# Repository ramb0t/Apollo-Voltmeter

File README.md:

Apollo-Voltmeter
================

Voltmeter Code for Design Two Module

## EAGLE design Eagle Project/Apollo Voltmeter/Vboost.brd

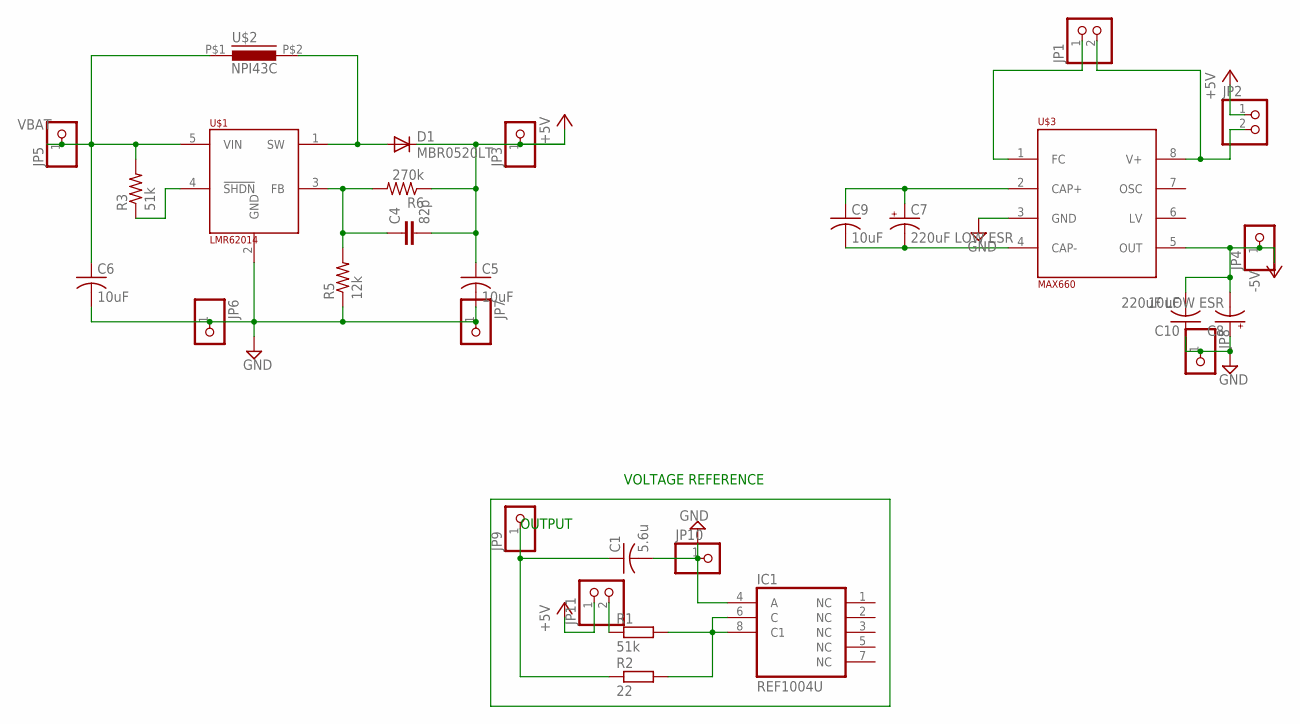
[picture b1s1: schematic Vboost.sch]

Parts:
C1: 5.6u; C0805K
C4: 82p; C0805
C5, C6, C9, C10: 10uF; C0805
C7, C8: 220uF LOW ESR; PANASONIC_D
D1: MBR0520LT; SOD123
IC1: REF1004U; SO08
JP1, JP2, JP11: PINHD-1X2; 1X02
JP3, JP4, JP5, JP6, JP7, JP8, JP9, JP10: PINHD-1X1; 1X01
R1: 51k; M0805
R2: 22; M0805
R3: 51k; R0805
R5: 12k; R0805
R6: 270k; R0805
U$1: LMR62014; SOT23-5
U$2: NPI43C
U$3: MAX660; SO08

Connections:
+5V: C4.2, C5.1, D1.C, JP2.1, JP3.1, JP11.1, R6.1
-5V: C8.-, C10.2, JP4.1, U$3.5 (OUT)
GND: C1.2, C5.2, C6.2, C8.+, C10.1, IC1.4 (A), JP6.1, JP7.1, JP8.1, JP10.1, R5.1, U$1.2 (GND), U$3.3 (GND)
unnamed: JP1.2, JP2.2, U$3.8 (V+)
unnamed: IC1.6 (C), IC1.8 (C1), R1.2, R2.2
unnamed: C1.1, JP9.1, R2.1
unnamed: C7.+, C9.1, U$3.2 (CAP+)
unnamed: JP11.2, R1.1
unnamed: R3.1, U$1.4 (!SHDN)
unnamed: C7.-, C9.2, U$3.4 (CAP-)
unnamed: C4.1, R5.2, R6.2, U$1.3 (FB)
unnamed: JP1.1, U$3.1 (FC)
SW: D1.A, U$1.1 (SW), U$2.P$2 (2)
VBAT: C6.1, JP5.1, R3.2, U$1.5 (VIN), U$2.P$1 (1)

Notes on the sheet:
OUTPUT
VOLTAGE REFERENCE

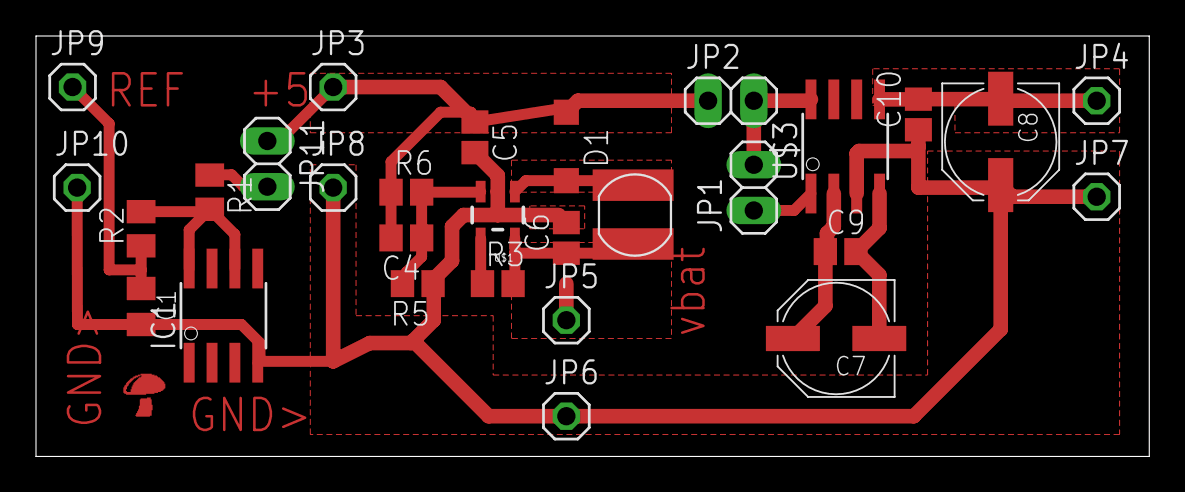
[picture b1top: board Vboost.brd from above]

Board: 2 copper layers, 61.8 x 23.4 mm, 29 parts (0 on the bottom side), 14 nets.

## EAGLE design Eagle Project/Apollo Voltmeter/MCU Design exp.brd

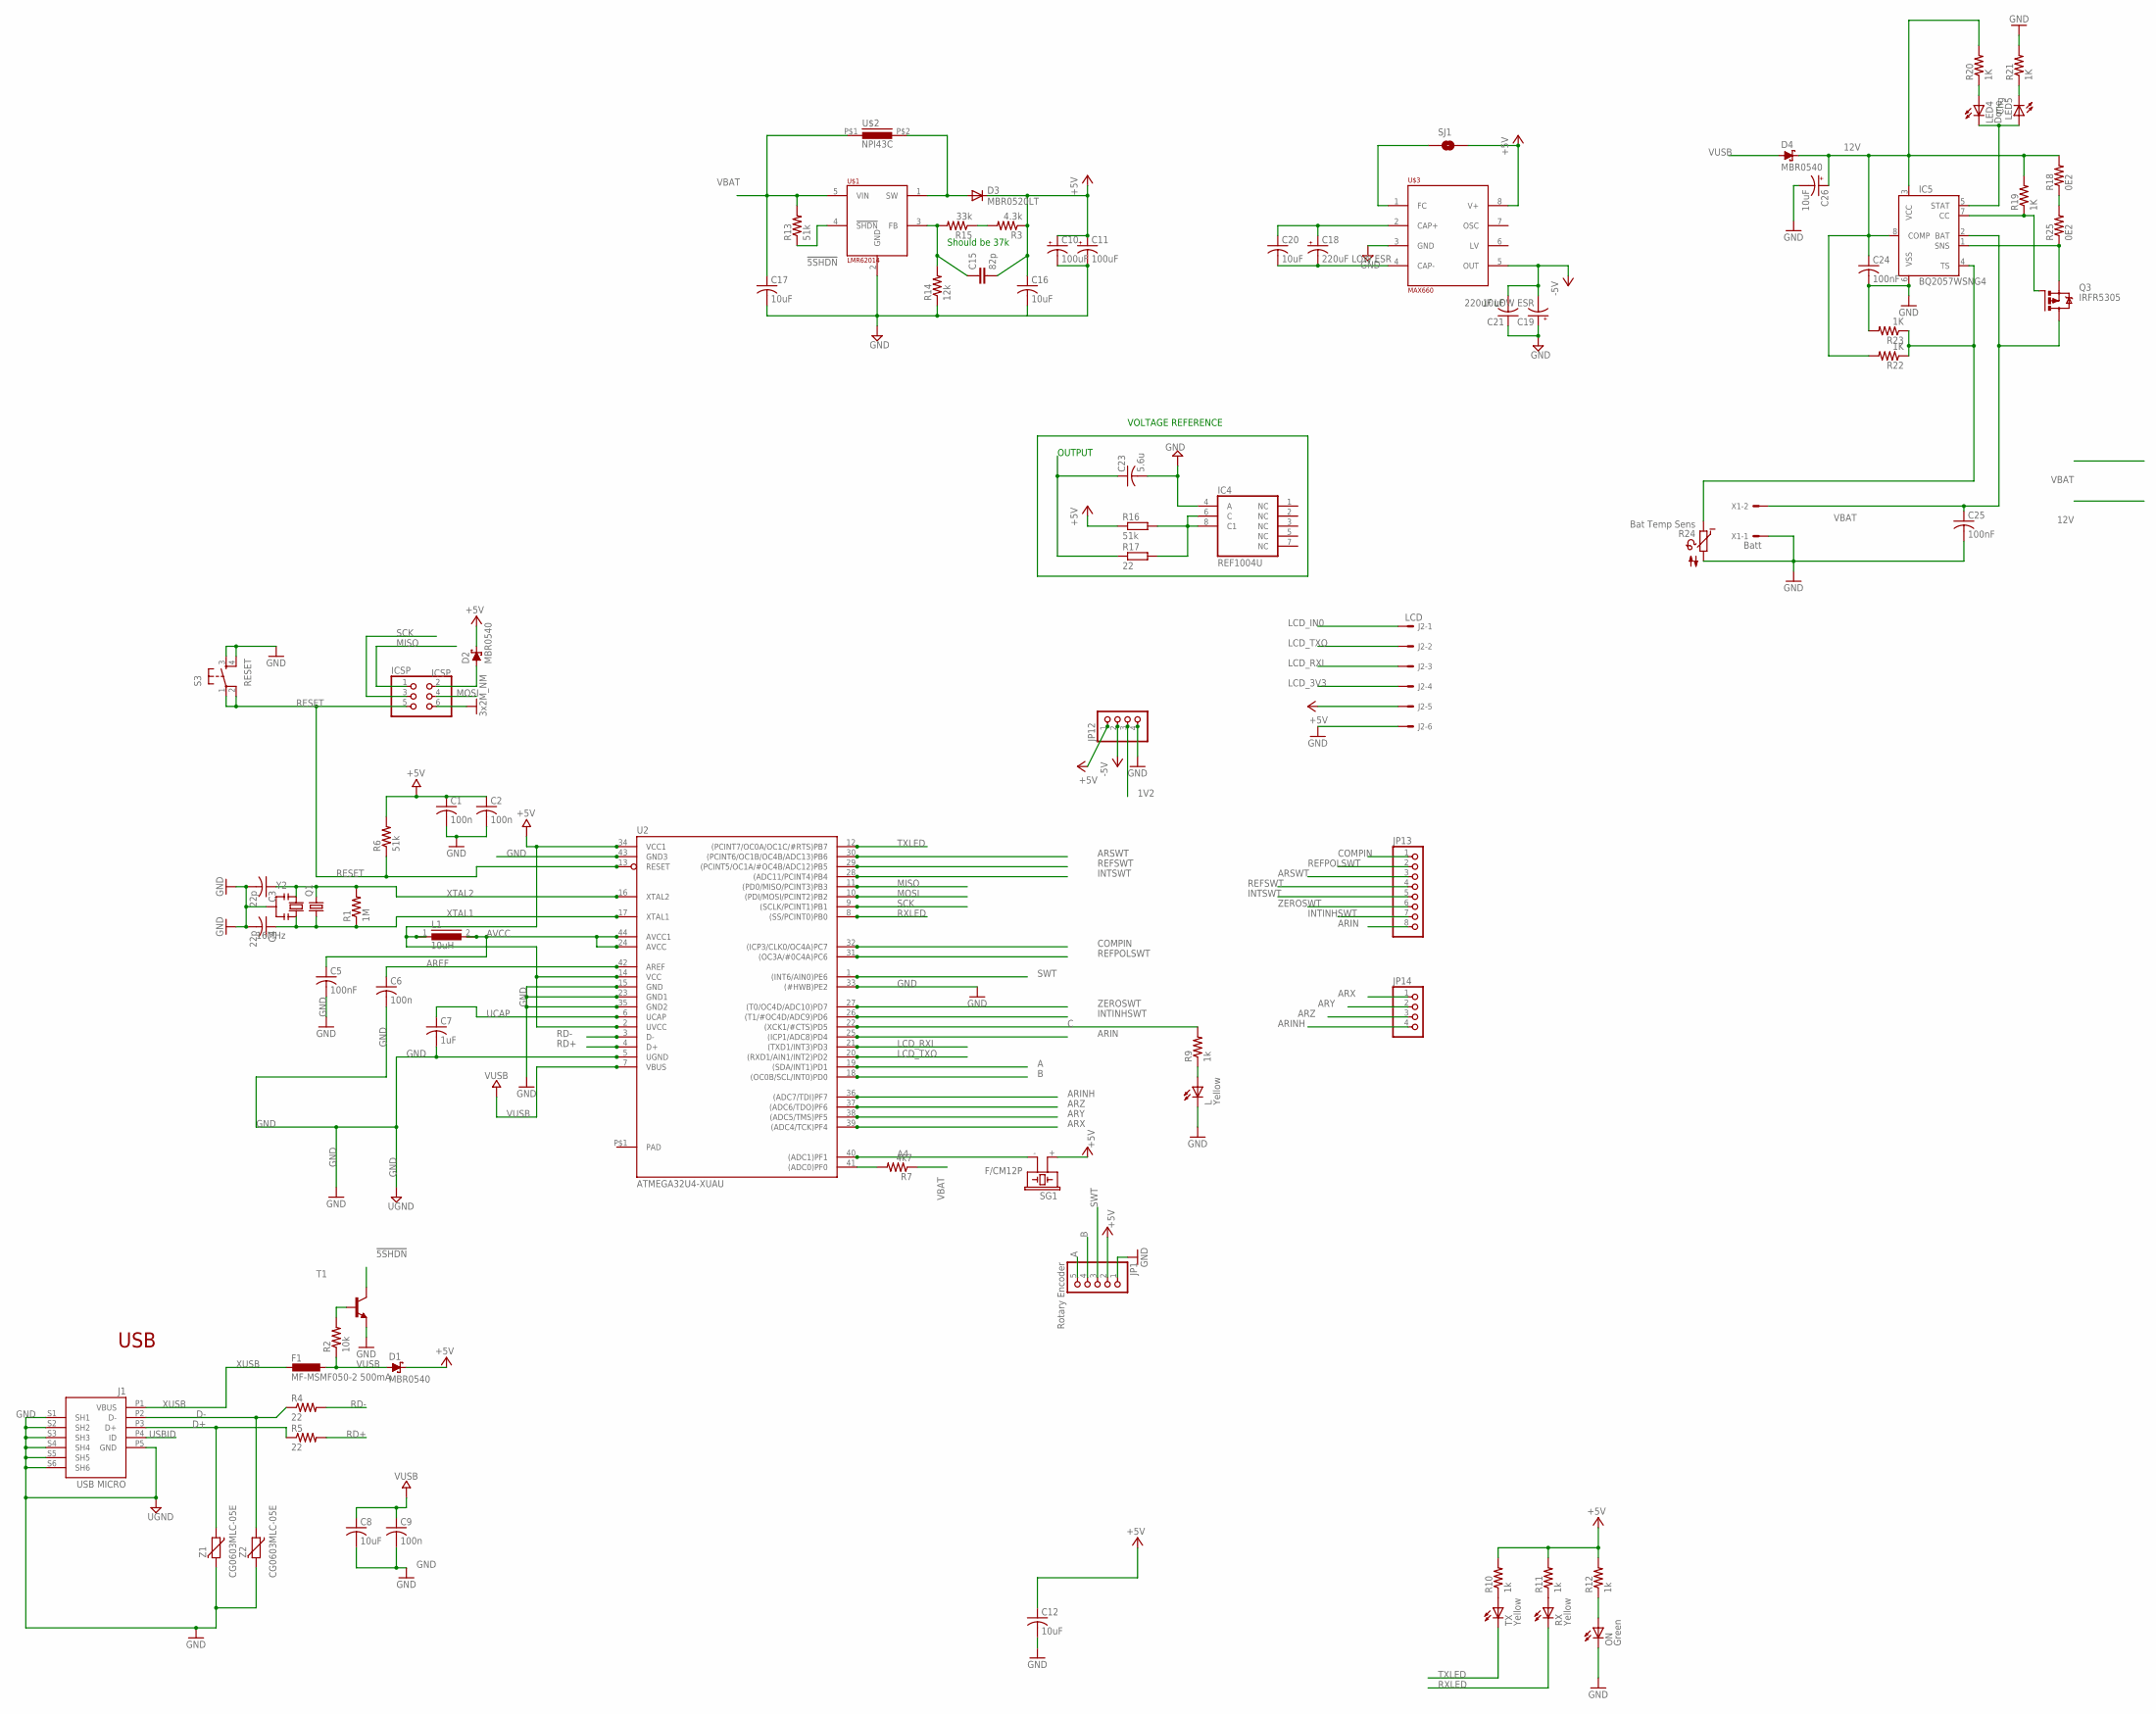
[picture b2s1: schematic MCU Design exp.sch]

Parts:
C1, C2, C6, C9: 100n; C0805
C3, C4: 22p; C0805
C5: 100nF; C0805
C7: 1uF; C0805
C8, C12, C16, C17, C20, C21: 10uF; C0805
C10, C11: 100uF; PANASONIC_D
C15: 82p; C0805
C18, C19: 220uF LOW ESR; PANASONIC_D
C23: 5.6u; C0805K
C24, C25: 100nF; C0805K
C26: 10uF; 153CLV-0405
D1, D2, D4: MBR0540; SOD123@2
D3: MBR0520LT; SOD123
F1: MF-MSMF050-2 500mA; L1812
IC4: REF1004U; SO08
IC5: BQ2057WSNG4; D_R-PDSO-G8
ICSP: ICSP; 2X03
J1: USB MICRO; CON2_USB_MICRO_B_AT
J2: LCD; 7395-06
JP1: Rotary Encoder; 1X05
JP12, JP14: PINHD-1X4; 1X04
JP13: PINHD-1X8; 1X08
L: Yellow; CHIPLED_0805
L1: 10uH; MMICC7
LED4: Done; CHIPLED_0805
LED5: Chg; CHIPLED_0805
ON: Green; CHIPLED_0805
Q1: CRYSTALHC49UP; HC49UP
Q3: IRFR5305; D-PAK_TO252AA
R1: 1M; R0805
R2: 10k; R0805
R3: 4.3k; R0805
R4, R5: 22; R0805
R6, R13: 51k; R0805
R7: 4k7; R0805
R9, R10, R11, R12: 1k; R0805
R14: 12k; R0805
R15: 33k; R0805
R16: 51k; M0805
R17: 22; M0805
R18, R25: 0E2; M1206
R19, R20, R21, R22, R23: 1K; R0805
R24: Bat Temp Sens; P640
RX: Yellow; CHIPLED_0805
S3: RESET; TACTILE_SWITCH_SMD
SG1: F/CM12P
SJ1: SOLDERJUMPERTRACE; SJ_2S-TRACE
T1: MMBT2222ALT1-NPN-SOT23-BEC; SOT23-BEC
TX: Yellow; CHIPLED_0805
U2: ATMEGA32U4-XUAU; TQFP44-PAD
U$1: LMR62014; SOT23-5
U$2: NPI43C
U$3: MAX660; SO08
X1: Batt; 22-23-2021
Y2: 16MHz; RESONATOR
Z1, Z2: CG0603MLC-05E; CT/CN0603

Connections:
1V2: C23.1, JP12.3, R17.1
12V: C24.1, C26.+, D4.C, IC5.3 (VCC), IC5.8 (COMP), R18.2, R19.2, R20.2, R22.2
!5SHDN: R13.1, T1.C, U$1.4 (!SHDN)
+5V: C1.1, C2.1, C10.+, C11.+, C12.1, C15.2, C16.1, D1.C, D2.C, D3.C, J2.5, JP1.2, JP12.1, L1.1, R3.1, R6.2, R10.2, R11.2, R12.2, R16.1, SG1.+ (1), SJ1.2, U2.2 (UVCC), U2.14 (VCC), U2.34 (VCC1), U$3.8 (V+)
-5V: C19.-, C21.2, JP12.2, U$3.5 (OUT)
A: JP1.5, U2.19 ((SDA/INT1)PD1)
A4: SG1.- (2), U2.40 ((ADC1)PF1)
AREF: C6.1, U2.42 (AREF)
ARIN: JP13.8, U2.25 ((ICP1/ADC8)PD4)
ARINH: JP14.4, U2.36 ((ADC7/TDI)PF7)
ARSWT: JP13.3, U2.30 ((PCINT6/OC1B/OC4B/ADC13)PB6)
ARX: JP14.1, U2.39 ((ADC4/TCK)PF4)
ARY: JP14.2, U2.38 ((ADC5/TMS)PF5)
ARZ: JP14.3, U2.37 ((ADC6/TDO)PF6)
AVCC: C5.1, L1.2, U2.24 (AVCC), U2.44 (AVCC1)
B: JP1.4, U2.18 ((OC0B/SCL/INT0)PD0)
C: R9.2, U2.22 ((XCK1/#CTS)PD5)
COMPIN: JP13.1, U2.32 ((ICP3/CLK0/OC4A)PC7)
D+: J1.P3 (D+), R5.1, Z1.1
D-: J1.P2 (D-), R4.1, Z2.1
GND: C1.2, C2.2, C3.2, C4.2, C5.2, C6.2, C7.2, C8.2, C9.2, C10.-, C11.-, C12.2, C16.2, C17.2, C19.+, C21.1, C23.2, C24.2, C25.2, C26.-, IC4.4 (A), IC5.6 (VSS), ICSP.6, J1.P5 (GND), J1.S1 (SH1), J1.S2 (SH2), J1.S3 (SH3), J1.S4 (SH4), J1.S5 (SH5), J1.S6 (SH6), J2.6, JP1.1, JP12.4, L.C, ON.C, R14.1, R21.2, R23.2, R24.2, S3.3, S3.4, T1.E, U2.5 (UGND), U2.15 (GND), U2.23 (GND1), U2.33 ((#HWB)PE2), U2.35 (GND2), U2.43 (GND3), U$1.2 (GND), U$3.3 (GND), X1.1, Y2.2, Z1.2, Z2.2
INTINHSWT: JP13.7, U2.26 ((T1/#OC4D/ADC9)PD6)
INTSWT: JP13.5, U2.28 ((ADC11/PCINT4)PB4)
LCD_3V3: J2.4
LCD_IN0: J2.1
LCD_RXI: J2.3, U2.21 ((TXD1/INT3)PD3)
LCD_TXO: J2.2, U2.20 ((RXD1/AIN1/INT2)PD2)
MISO: ICSP.1, U2.11 ((PD0/MISO/PCINT3)PB3)
MOSI: ICSP.4, U2.10 ((PDI/MOSI/PCINT2)PB2)
unnamed: R10.1, TX.A
unnamed: L.A, R9.1
unnamed: ON.A, R12.1
unnamed: R11.1, RX.A
unnamed: C18.+, C20.1, U$3.2 (CAP+)
unnamed: R7.2, U2.41 ((ADC0)PF0)
unnamed: IC4.6 (C), IC4.8 (C1), R16.2, R17.2
unnamed: R2.2, T1.B
unnamed: D2.A, ICSP.2
unnamed: R3.2, R15.1
unnamed: IC5.5 (STAT), LED4.C, LED5.A
unnamed: LED4.A, R20.1
unnamed: R18.1, R25.2
unnamed: C18.-, C20.2, U$3.4 (CAP-)
unnamed: C15.1, R14.2, R15.2, U$1.3 (FB)
unnamed: SJ1.1, U$3.1 (FC)
unnamed: IC5.1 (SNS), Q3.3 (S), R25.1
unnamed: IC5.7 (CC), Q3.1 (G), R19.1
unnamed: LED5.C, R21.1
unnamed: IC5.4 (TS), R22.1, R23.1, R24.1
PAD: U2.P$1 (PAD)
RD+: R5.2, U2.4 (D+)
RD-: R4.2, U2.3 (D-)
REFPOLSWT: JP13.2, U2.31 ((OC3A/#0C4A)PC6)
REFSWT: JP13.4, U2.29 ((PCINT5/OC1A/#OC4B/ADC12)PB5)
RESET: ICSP.5, R6.1, S3.1, S3.2, U2.13 (RESET)
RXLED: RX.C, U2.8 ((SS/PCINT0)PB0)
SCK: ICSP.3, U2.9 ((SCLK/PCINT1)PB1)
SW: D3.A, U$1.1 (SW), U$2.P$2 (2)
SWT: JP1.3, U2.1 ((INT6/AIN0)PE6)
TXLED: TX.C, U2.12 ((PCINT7/OC0A/OC1C/#RTS)PB7)
UCAP: C7.1, U2.6 (UCAP)
USBID: J1.P4 (ID)
VBAT: C17.1, C25.1, IC5.2 (BAT), Q3.4 (D), R7.1, R13.2, U$1.5 (VIN), U$2.P$1 (1), X1.2
VUSB: C8.1, C9.1, D1.A, D4.A, F1.1, R2.1, U2.7 (VBUS)
XTAL1: C4.1, Q1.1, R1.1, U2.17 (XTAL1), Y2.3
XTAL2: C3.1, Q1.2, R1.2, U2.16 (XTAL2), Y2.1
XUSB: F1.2, J1.P1 (VBUS)
ZEROSWT: JP13.6, U2.27 ((T0/OC4D/ADC10)PD7)

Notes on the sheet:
USB
OUTPUT
VOLTAGE REFERENCE
Should be 37k

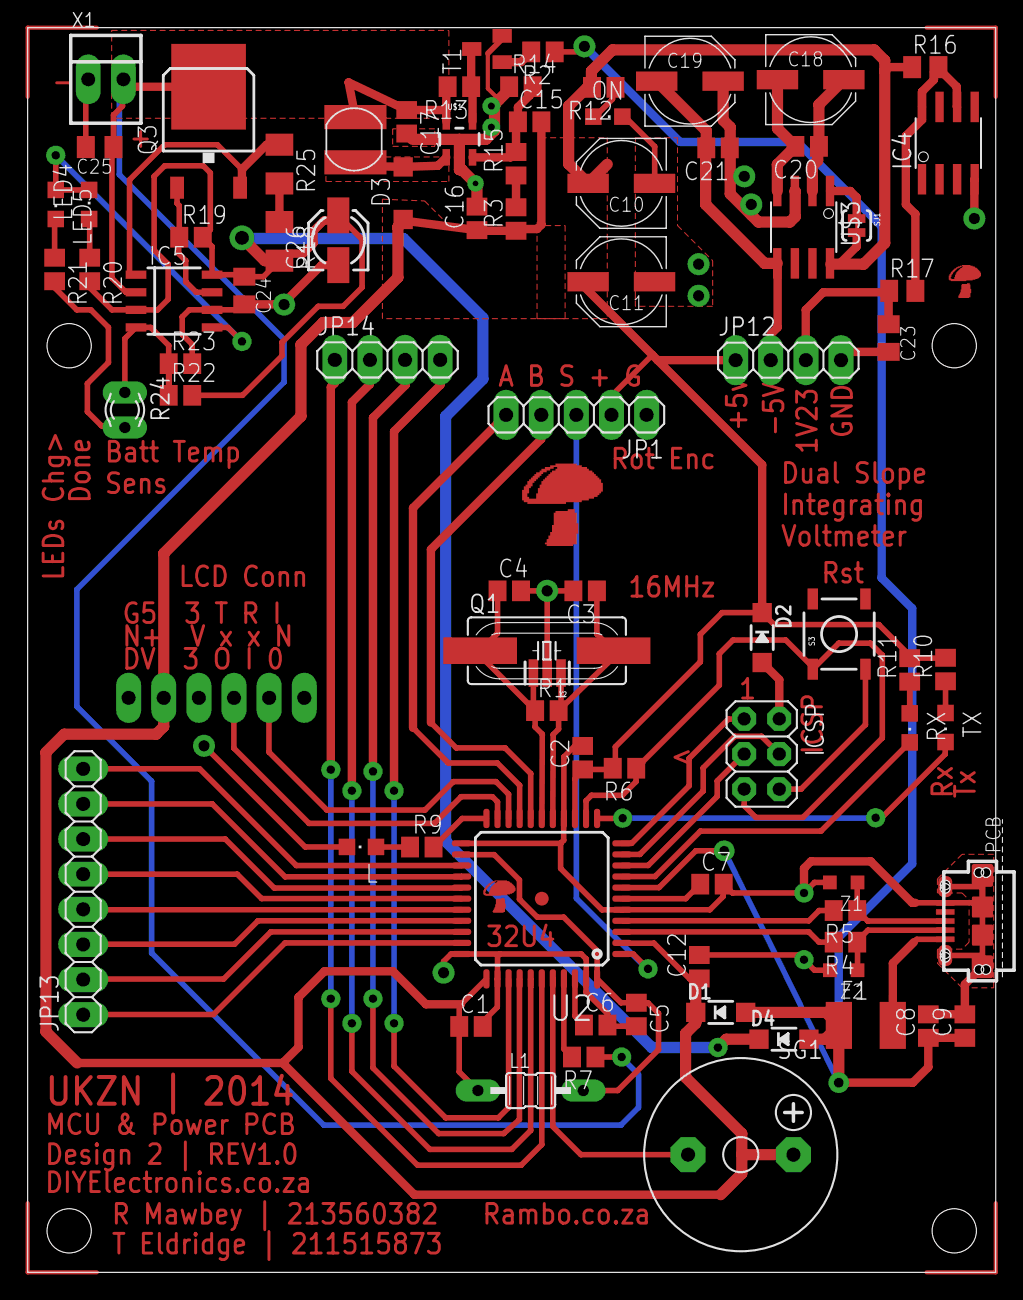
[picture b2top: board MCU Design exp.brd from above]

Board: 2 copper layers, 70.0 x 90.0 mm, 82 parts (1 on the bottom side), 64 nets.

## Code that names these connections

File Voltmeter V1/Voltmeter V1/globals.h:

/*
 * globals.h
 *
 * Created: 2014/09/28 11:16:14 AM
 *  Author: RobThePyro
 */ 

#ifndef	GLOBALS_H_
#define GLOBALS_H_

/* Intergration Defines */
#define ZERO_TIME  30
#define INT_TIME  80
#define INT_TIME_US	80000
#define DINT_TIME  160
#define VREF_MV		1086

/* Pin Defines: */
#define RXLED		PORTB, 0 // Active Low
#define SCK			PORTB, 1 // SPI
#define MOSI		PORTB, 2 // SPI
#define MISO		PORTB, 3 // SPI
#define IntSwt		PORTB, 4
#define RefSwt		PORTB, 5
#define ARSwt		PORTB, 6
#define TXLED		PORTB, 7 // Active Low

#define RefPolSwt	PORTC, 6
#define CompIn		PINC, 7	 // Input ICP3

#define ENC_A_IN	PIND, 0  // INT0
#define ENC_B_IN	PIND, 1  // INT1
#define LCD_TXO		PORTD, 2 // USART Tx
#define LCD_RXI		PORTD, 3 // USART Rx
#define ARIn		PIND, 4  // Input ICP1
#define StatusLED	PORTD, 5 // Active High
#define IntInhSwt	PORTD, 6
#define ZeroSwt		PORTD, 7

#define HWB			PORTE, 2 // Tied to GND
#define ENC_Swt		PINE, 6  // INT6

#define VBAT		PORTF, 0 // ADC0
#define BUZZ		PORTF, 1
#define ARX			PORTF, 4
#define ARY			PORTF, 5
#define ARZ			PORTF, 6
#define ARInh		PORTF, 7


#define PORTB_OUTS  (1<<0)|(1<<4)|(1<<5)|(1<<6)|(1<<7)
#define PORTB_INS
#define PORTC_OUTS	(1<<6)
#define PORTC_INS	(1<<7)
#define PORTD_OUTS	(1<<2)|(1<<5)|(1<<6)|(1<<7)
#define PORTD_INS	(1<<0)|(1<<1)|(1<<3)|(1<<4)
#define PORTE_OUTS
#define PORTE_INS	(1<<2)|(1<<6)
#define PORTF_OUTS	(1<<1)|(1<<4)|(1<<5)|(1<<6)|(1<<7)
#define PORTF_INS	(1<<0)

/* Range Defines */
#define RANGE4	 0
#define RANGE40	 1
#define RANGE400 2

/* 9600 baud */
#define UART_BAUD_RATE      9600

/* LCD Command defines */
#define	CMD_RESULT0	0xF0
#define CMD_RESULT1 0xF2

#define	CMD_BATT0	0xF7
#define CMD_BATT1	0xF8

#define CMD_BACKLIGHT0 0xF5
#define CMD_BACKLIGHT1 0xF6

#define CMD_RANGE0 0xF9
#define CMD_RANGE1 0xF1

/* ADC Defines */ 
#define ADC_AVcc_VALUE			5050 //mV
#define ADC_VBAT_CHANNEL	0x00


#endif

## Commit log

2014-08-31 First commit moving to github
2014-08-31 Testing out alt lcd driver
2014-08-31 LCD working!
2014-08-31 First Working Copy!
2014-09-25 Started work on final code, hardware usart to lcd working!
2014-09-29 Working code on final Apollo board without AFE
2014-09-30 Working version :) still more to do...
2014-09-30 Modified bootloader to timeout just like arduino!
2014-09-30 Version used for presentation, still not ideal..
2014-11-26 Tidy up!
2015-02-22 #admin...
2015-03-23 Added eagle files
2015-06-28 Moar Tidy ?

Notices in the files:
parts and their libraries:
SparkFun: Licensing: CC v3.0 Share-Alike You are welcome to use this library for commercial purposes.
